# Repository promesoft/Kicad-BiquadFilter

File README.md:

# KicadBiquadFilter
Manually variable stereo filter (BP, HP, LP) in two sections

## Status - Rev A Produced Both sections operational
### Errata
 * Section 2 feedback OpAmp incorrect - has to be bypassed
 * Footprint of Op Amp little too small for the packages in stock
 
### Issues and Notes
Issues

Wishlist for Rev B 
 - should handle connectors and Potmeters on the PCB
 - Potmeters should have optional resistor in series and parallel
 - Section 1 adjustable: R5/6 stereo 100k + 680R and R11/13 stereo 20k + 680R
 - Capacitors as THT 47nF polyprop
 - Focus on Eurorack compatibility
 - Mono filter 
 - VCF option

## Physical Construction
 - 100x100mm
 - Several resistors has been selected as THT components so a Potmeter can be placed instead
 
The board is split in two, joined at the center of the board. Each section is a stereo section that can operate individually.
### Section 1 - State Variable filter and buffer amp

### Section 2 - State Variable filter and regulator

## Vital Components
 - Op Amp is chosen as MC33078 but can be selected as long as its pin compatible like (ua833, TL062, TL072, TL082, etc)

### Section 1 Filter components for High Q variable freq and Q:
 - R8 / R5   - 680R + 100k Stereo Pot
 - R10 / R7  - 680R + 100k Stereo Pot
 - R3 / R1   - 47k
 - R4 / R2   - 47k
 - R9 / R6   - 47k
 - R12 / R11 - 680R + 20k Stereo Pot
 - R14 / R13 - 680R + 20k Stereo Pot
 - R16 / C15 - 47nF
 - R18 / C17 - 47nF
 
Fc - 163Hz - 5KHz 

Q - 0,68 - 6,9

## Features
The state variable filter can be configured in different ways and needs to be calculated before the components are selected.

https://www.electronics-tutorials.ws/filter/state-variable-filter.html

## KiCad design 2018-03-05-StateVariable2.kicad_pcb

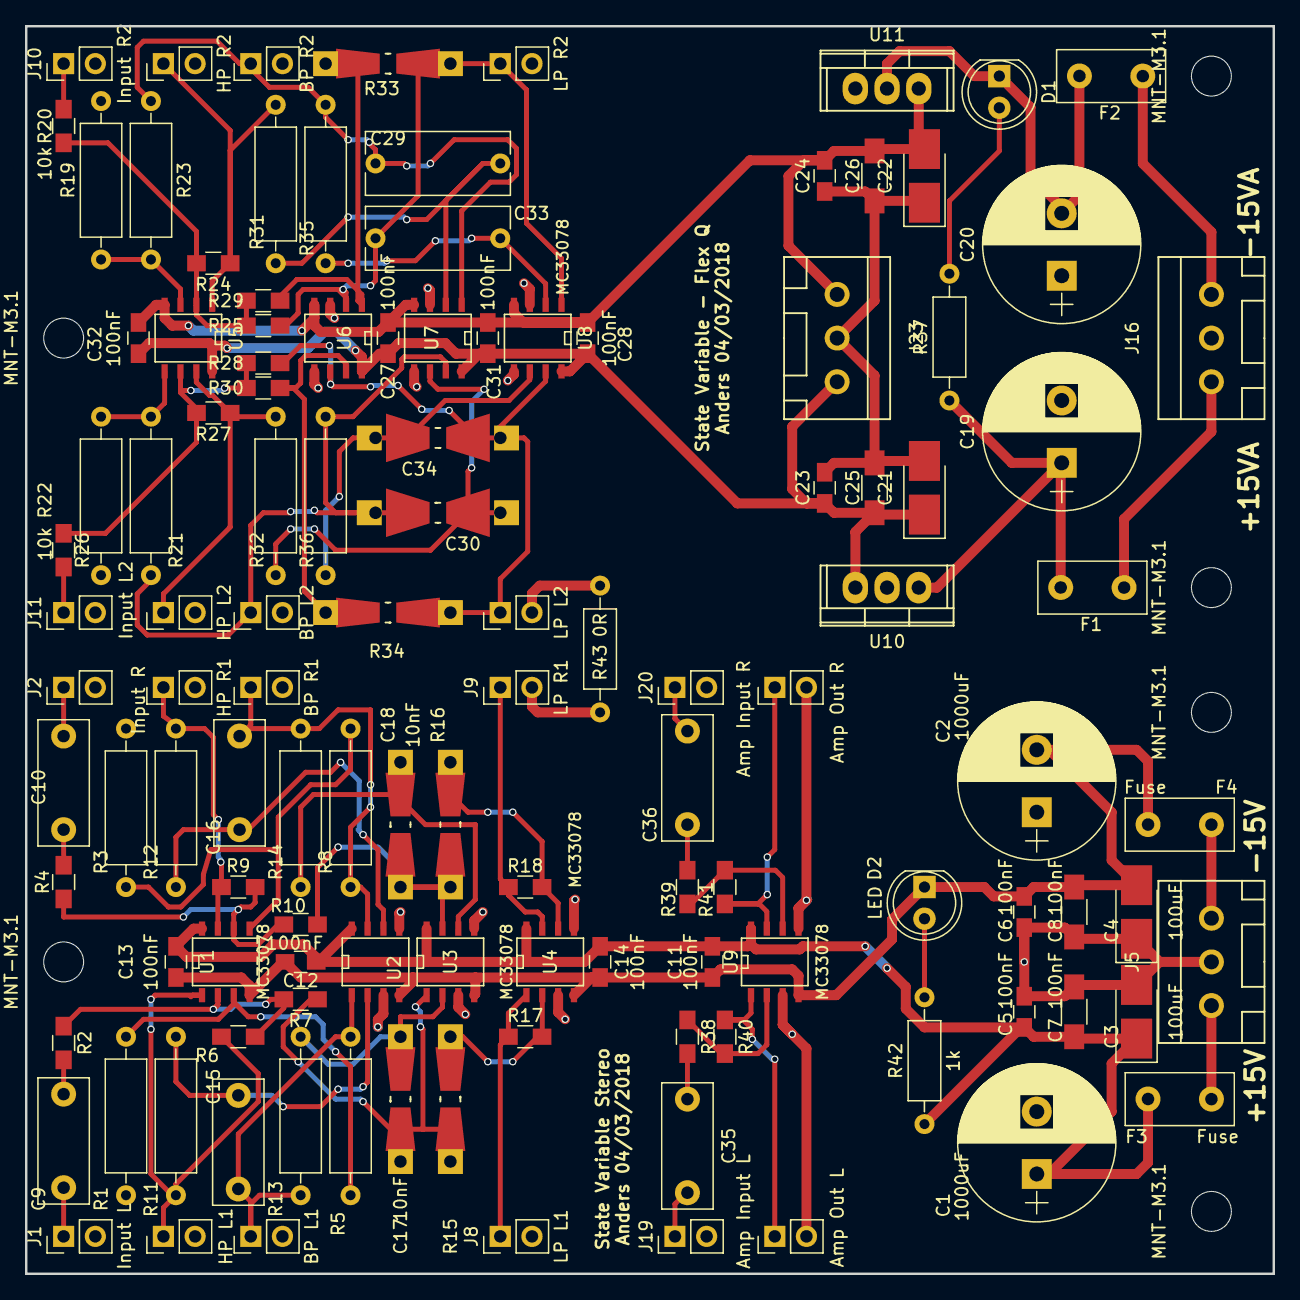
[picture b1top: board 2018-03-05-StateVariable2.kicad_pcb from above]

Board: 2 copper layers, 100.0 x 100.0 mm, 125 parts (0 on the bottom side), 61 nets.

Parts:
C1, C2, C19, C20: 1000uF; CP_Radial_D12.5mm_P5.00mm
C3, C4, C21, C22: 100uF; CP_Tantalum_Case-B_EIA-3528-21_Hand
C5, C6, C11, C12, C13, C14, C23, C24, C27, C28, C31, C32: 100nF; C_0805_HandSoldering
C7, C8, C25, C26: 100nF; C_1206_HandSoldering
C9, C10, C35, C36: C; C_Rect_L10.0mm_W4.0mm_P7.50mm_MKS4
C15, C16: 10nF; C_Rect_L10.0mm_W4.0mm_P7.50mm_MKS4
C17, C18: 10nF; Resistor_SMD+THTuniversal_0805to1206_RM10_HandSoldering
C29, C33: 10nF; C_Rect_L11.5mm_W5.0mm_P10.00mm_MKT
C30, C34: 10nF; Resistor_SMD+THTuniversal_0805to2512_RM10_HandSoldering
D1, D2: LED; LED_D5.0mm
F1, F2, F3, F4: Fuse; Fuse_TE5_Littlefuse-395Series
J1: Input L; Pin_Header_Straight_1x02_Pitch2.54mm
J2: Input R; Pin_Header_Straight_1x02_Pitch2.54mm
J3: HP L1; Pin_Header_Straight_1x02_Pitch2.54mm
J4: HP R1; Pin_Header_Straight_1x02_Pitch2.54mm
J5, J16, J23: Power; WAGO_734_3pin_Straight
J6: BP L1; Pin_Header_Straight_1x02_Pitch2.54mm
J7: BP R1; Pin_Header_Straight_1x02_Pitch2.54mm
J8: LP L1; Pin_Header_Straight_1x02_Pitch2.54mm
J9: LP R1; Pin_Header_Straight_1x02_Pitch2.54mm
J10: Input R2; Pin_Header_Straight_1x02_Pitch2.54mm
J11: Input L2; Pin_Header_Straight_1x02_Pitch2.54mm
J12: HP R2; Pin_Header_Straight_1x02_Pitch2.54mm
J13: HP L2; Pin_Header_Straight_1x02_Pitch2.54mm
J14: BP R2; Pin_Header_Straight_1x02_Pitch2.54mm
J15: BP L2; Pin_Header_Straight_1x02_Pitch2.54mm
J17: LP R2; Pin_Header_Straight_1x02_Pitch2.54mm
J18: LP L2; Pin_Header_Straight_1x02_Pitch2.54mm
J19: Amp Input L; Pin_Header_Straight_1x02_Pitch2.54mm
J20: Amp Input R; Pin_Header_Straight_1x02_Pitch2.54mm
J21: Amp Out L; Pin_Header_Straight_1x02_Pitch2.54mm
J22: Amp Out R; Pin_Header_Straight_1x02_Pitch2.54mm
MNT-M3.1, MNT-M3.1#2, MNT-M3.1#3, MNT-M3.1#4, MNT-M3.1#5, MNT-M3.1#6: MountingHole_3.2mm_M3
R1, R3, R5, R8, R11, R12, R13, R14, R19, R21, R23, R26, R31, R32, R35, R36: 10k; R_Axial_DIN0309_L9.0mm_D3.2mm_P12.70mm_Horizontal
R2, R4, R6, R7, R9, R10, R17, R18, R20, R22, R24, R25, R27, R28, R29, R30, R38, R39, R40, R41: 10k; R_0805_HandSoldering
R15, R16, R33, R34: 10k; Resistor_SMD+THTuniversal_0805to1206_RM10_HandSoldering
R37, R42: 1k; R_Axial_DIN0207_L6.3mm_D2.5mm_P10.16mm_Horizontal
R43: 0R; R_Axial_DIN0207_L6.3mm_D2.5mm_P10.16mm_Horizontal
U1, U2, U3, U4, U5, U6, U7, U8, U9: MC33078; SO-8
U10: L7812; TO-220
U11: L7912; TO-220

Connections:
+12VA: C21.1, C23.1, C25.1, C27.1, C28.1, C31.1, C32.1, J23.3, U5.8, U6.8, U7.8, U8.8, U10.3
-12VA: C22.2, C24.2, C26.2, C27.2, C28.2, C31.2, C32.2, J23.1, U5.4, U6.4, U7.4, U8.4, U11.3
GNDA: C1.2, C2.1, C3.2, C4.1, C5.2, C6.1, C7.2, C8.1, C19.2, C20.1, C21.2, C22.1, C23.2, C24.1, C25.2, C26.1, J1.2, J2.2, J3.2, J4.2, J5.2, J6.2, J7.2, J8.2, J9.2, J10.2, J11.2, J12.2, J13.2, J14.2, J15.2, J16.2, J17.2, J18.2, J19.2, J20.2, J21.2, J22.2, J23.2, R1.2, R3.2, R19.2, R21.2, R43.1, R43.2, U2.3, U2.5, U3.3, U3.5, U4.3, U4.5, U6.3, U6.5, U7.3, U7.5, U8.3, U8.5, U9.3, U9.5, U10.2, U11.1
unnamed: C9.1, R2.2
unnamed: C9.2, J1.1
unnamed: C10.1, R4.2
unnamed: C10.2, J2.1
unnamed: C15.1, J6.1, R5.1, R13.2, U2.1
unnamed: C15.2, R11.1, U2.2
unnamed: C16.1, J7.1, R8.1, R14.2, U2.7
unnamed: C16.2, R12.1, U2.6
unnamed: C17.1, R7.1, R15.2, U3.1
unnamed: C17.2, R13.1, U3.2
unnamed: C18.1, R10.1, R16.2, U3.7
unnamed: C18.2, R14.1, U3.6
unnamed: C19.1, F1.2, R37.1, U10.1
unnamed: C20.2, D1.1, F2.2, U11.2
unnamed: C29.1, J14.1, R23.1, R35.2, U7.1
unnamed: C29.2, R31.1, U7.2
unnamed: C30.1, J15.1, R26.1, R36.2, U7.7
unnamed: C30.2, R32.1, U7.6
unnamed: C33.1, J17.1, R25.1, R33.1, U6.2, U8.1
unnamed: C33.2, R35.1, U8.2
unnamed: C34.1, J18.1, R28.1, R34.1, U6.6, U8.7
unnamed: C34.2, R36.1, U8.6
unnamed: C35.1, R38.2
unnamed: C35.2, J19.1
unnamed: C36.1, R39.2
unnamed: C36.2, J20.1
unnamed: D1.2, R37.2
unnamed: D2.2, R42.2
unnamed: F1.1, J16.1
unnamed: F2.1, J16.3
unnamed: F3.1, J5.1
unnamed: F4.1, J5.3
unnamed: J3.1, R6.1, R11.2, U1.1
unnamed: J4.1, R9.1, R12.2, U1.7
unnamed: J8.1, R17.1, U4.1
unnamed: J9.1, R18.1, U4.7
unnamed: J10.1, R20.2
unnamed: J11.1, R22.2
unnamed: J12.1, R24.1, R31.2, U5.1
unnamed: J13.1, R27.1, R32.2, U5.7
unnamed: J21.1, R40.1, U9.1
unnamed: J22.1, R41.1, U9.7
unnamed: R1.1, R5.2, U1.3
unnamed: R2.1, R6.2, R7.2, U1.2
unnamed: R3.1, R8.2, U1.5
unnamed: R4.1, R9.2, R10.2, U1.6
unnamed: R15.1, R17.2, U4.2
unnamed: R16.1, R18.2, U4.6
unnamed: R19.1, R23.2, U5.3
unnamed: R20.1, R24.2, R25.2, R29.2, U5.2
unnamed: R21.1, R26.2, U5.5
unnamed: R22.1, R27.2, R28.2, R30.2, U5.6
unnamed: R29.1, R33.2, U6.1
unnamed: R30.1, R34.2, U6.7
unnamed: R38.1, R40.2, U9.2
unnamed: R39.1, R41.2, U9.6
VCC: C1.1, C3.1, C5.1, C7.1, C11.1, C12.1, C13.1, C14.1, F3.2, R42.1, U1.8, U2.8, U3.8, U4.8, U9.8
VEE: C2.2, C4.2, C6.2, C8.2, C11.2, C12.2, C13.2, C14.2, D2.1, F4.2, U1.4, U2.4, U3.4, U4.4, U9.4

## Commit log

2019-01-10 Init
    Project moved from Statevar2
2019-01-10 Schematic
2019-01-18 Schematics images
2019-01-19 Readme - filter calc for modular filter
2019-01-19 Update README.md
    Update Fc and Q
2019-01-19 RevA consolidate
